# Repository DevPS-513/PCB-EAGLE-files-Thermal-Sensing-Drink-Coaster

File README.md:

PCB files for temperature sensor drink coaster project

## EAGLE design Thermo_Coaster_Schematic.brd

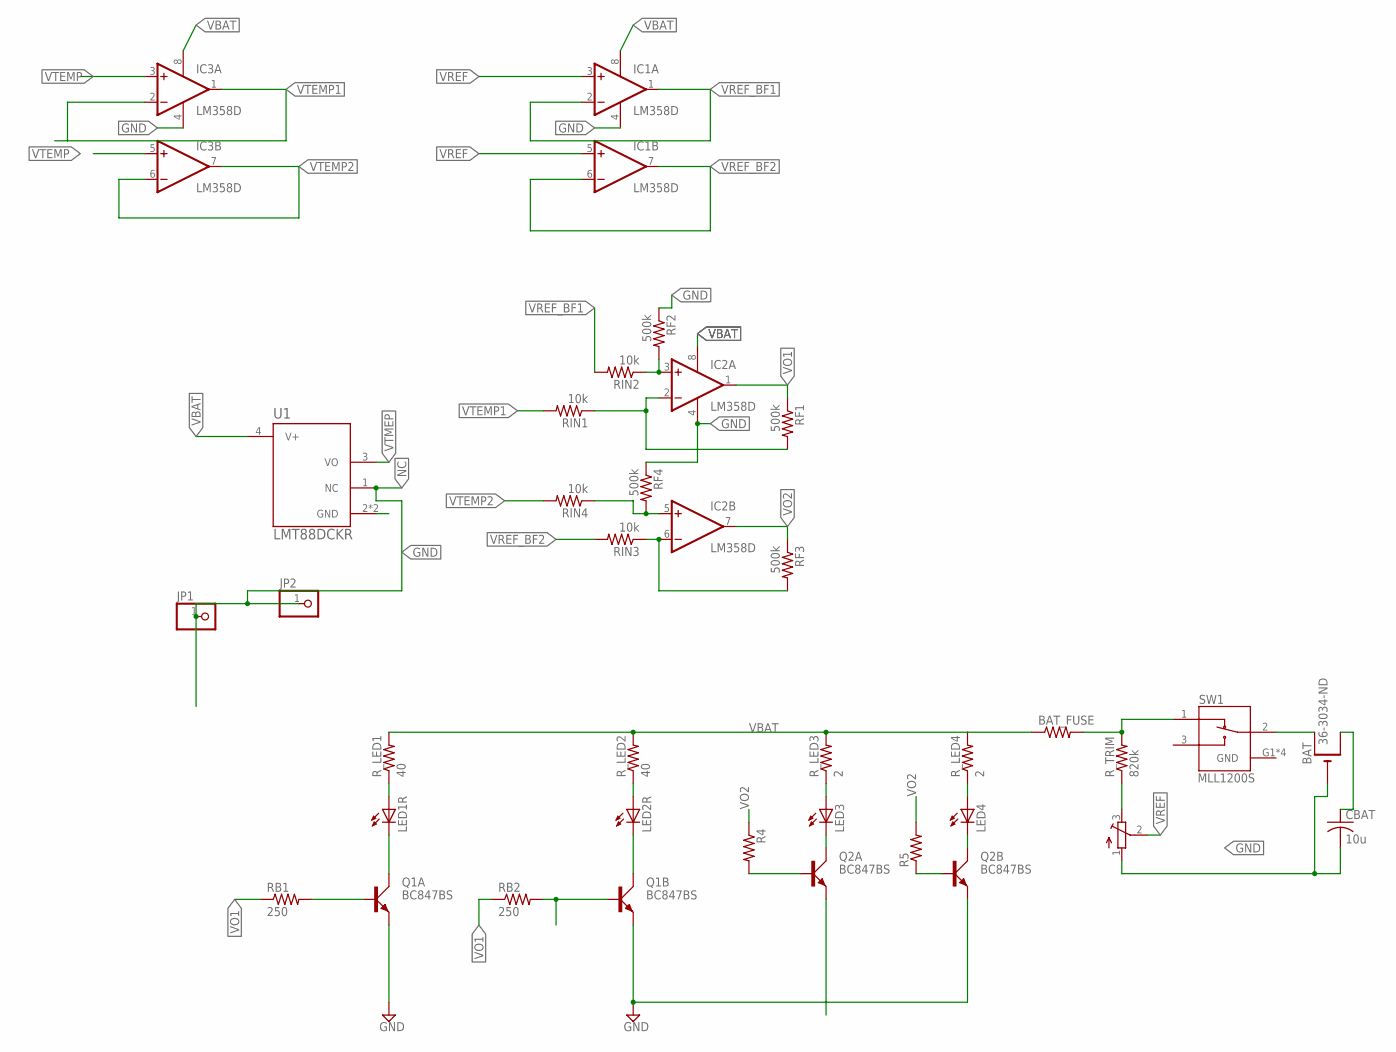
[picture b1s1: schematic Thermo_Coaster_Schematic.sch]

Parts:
BAT: CR1220SMT; CR1220-SMD
BAT_FUSE: R-US_R1206; R1206
CBAT: 10u; C1206
IC1, IC2, IC3: LM358D; SO08
JP1, JP2: PINHD-1X1; 1X01
LED1R, LED2R, LED3, LED4: LEDCHIPLED_1206; CHIPLED_1206
Q1, Q2: BC847BS; SOT363_PHILIPS
R4, R5: R-US_R0805; R0805
RB1, RB2: 250; R0805
RF1, RF2, RF3, RF4: 500k; R0805
RIN1, RIN2, RIN3, RIN4: 10k; R0805
R_LED1, R_LED2: 40; R0805
R_LED3, R_LED4: 2; R0805
R_TRIM: 820k; R0805
SW1: MLL1200S; SW_MLL1200S
TRIM_VREF: TRIMPOTTC33X; TC33X
U1: LMT88DCKR; SOT65P210X110-5N

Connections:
GND: BAT.-, CBAT.2, IC1.4 (V-), IC2.4 (V-), IC3.4 (V-), Q1.1 (E), Q1.4 (E), Q2.1 (E), Q2.4 (E), RF2.1, RF4.1, SW1.G1 (GND), SW1.G2 (GND), SW1.G3 (GND), SW1.G4 (GND), TRIM_VREF.1 (A), U1.2 (GND), U1.5 (GND)
unnamed: Q1.2 (B), RB1.2
unnamed: BAT_FUSE.2, R_TRIM.2, SW1.1
unnamed: LED2R.A, R_LED2.1
unnamed: Q1.5 (B), RB2.2
unnamed: LED1R.A, R_LED1.1
unnamed: LED1R.C, Q1.6 (C)
unnamed: LED2R.C, Q1.3 (C)
unnamed: LED3.A, R_LED3.1
unnamed: BAT.+$2 (+1), CBAT.1
unnamed: IC2.3 (+IN), RF2.2, RIN2.1
unnamed: LED4.A, R_LED4.1
unnamed: LED3.C, Q2.6 (C)
unnamed: BAT.+$1 (+), SW1.2
unnamed: LED4.C, Q2.3 (C)
unnamed: R_TRIM.1, TRIM_VREF.3 (E)
unnamed: IC2.2 (-IN), RF1.2, RIN1.1
unnamed: IC2.6 (-IN), RF3.2, RIN3.1
unnamed: IC2.5 (+IN), RF4.2, RIN4.1
NC: JP1.1, JP2.1, U1.1 (NC)
VBAT: BAT_FUSE.1, IC1.8 (V+), IC2.8 (V+), IC3.8 (V+), R_LED1.2, R_LED2.2, R_LED3.2, R_LED4.2, U1.4 (V+)
VO1: IC2.1 (OUT), RB1.1, RB2.1, RF1.1
VO2: IC2.7 (OUT), Q2.2 (B), Q2.5 (B), R4.1, R4.2, R5.1, R5.2, RF3.1
VREF: IC1.3 (+IN), IC1.5 (+IN), TRIM_VREF.2 (S)
VREF_BF1: IC1.1 (OUT), IC1.2 (-IN), RIN2.2
VREF_BF2: IC1.6 (-IN), IC1.7 (OUT), RIN3.2
VTEMP: IC3.3 (+IN), IC3.5 (+IN)
VTEMP1: IC3.1 (OUT), IC3.2 (-IN), RIN1.2
VTEMP2: IC3.6 (-IN), IC3.7 (OUT), RIN4.2
VTMEP: U1.3 (VO)

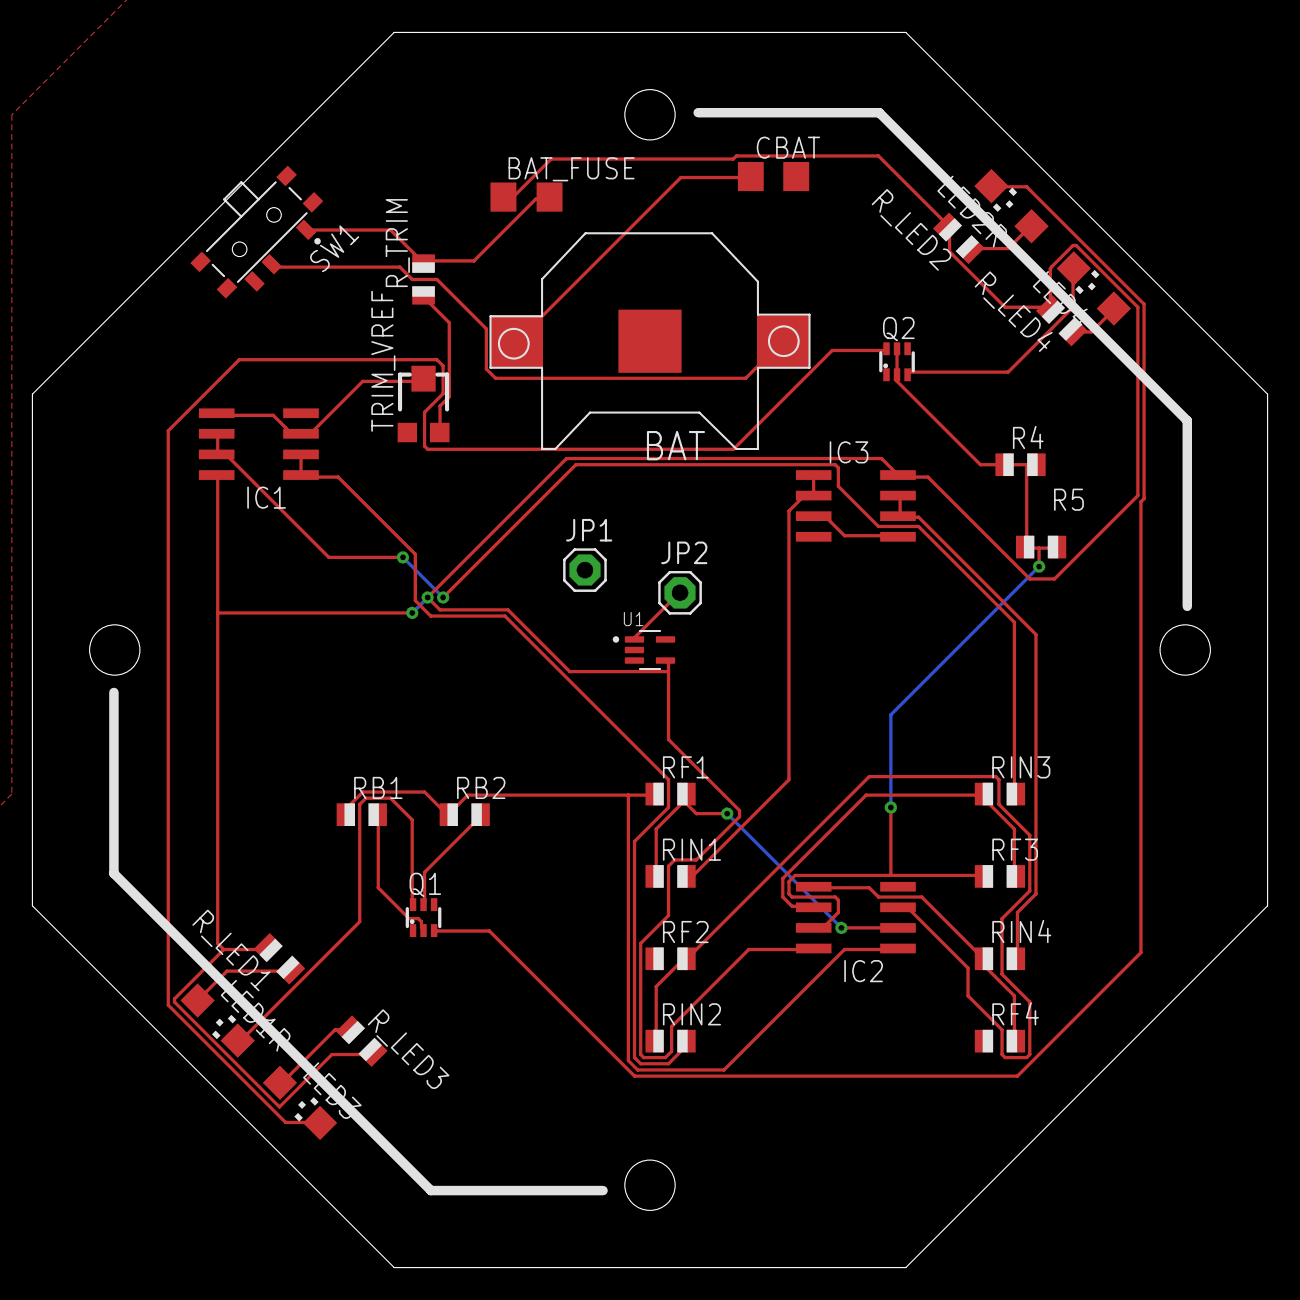
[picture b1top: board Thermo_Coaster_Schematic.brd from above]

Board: 2 copper layers, 76.2 x 76.2 mm, 34 parts (0 on the bottom side), 29 nets.

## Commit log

2021-01-05 first commit, about to solder on components
